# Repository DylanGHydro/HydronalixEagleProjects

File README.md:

View this project on [CADLAB.io](https://cadlab.io/project/1390). 

# HydronalixEagleProjects

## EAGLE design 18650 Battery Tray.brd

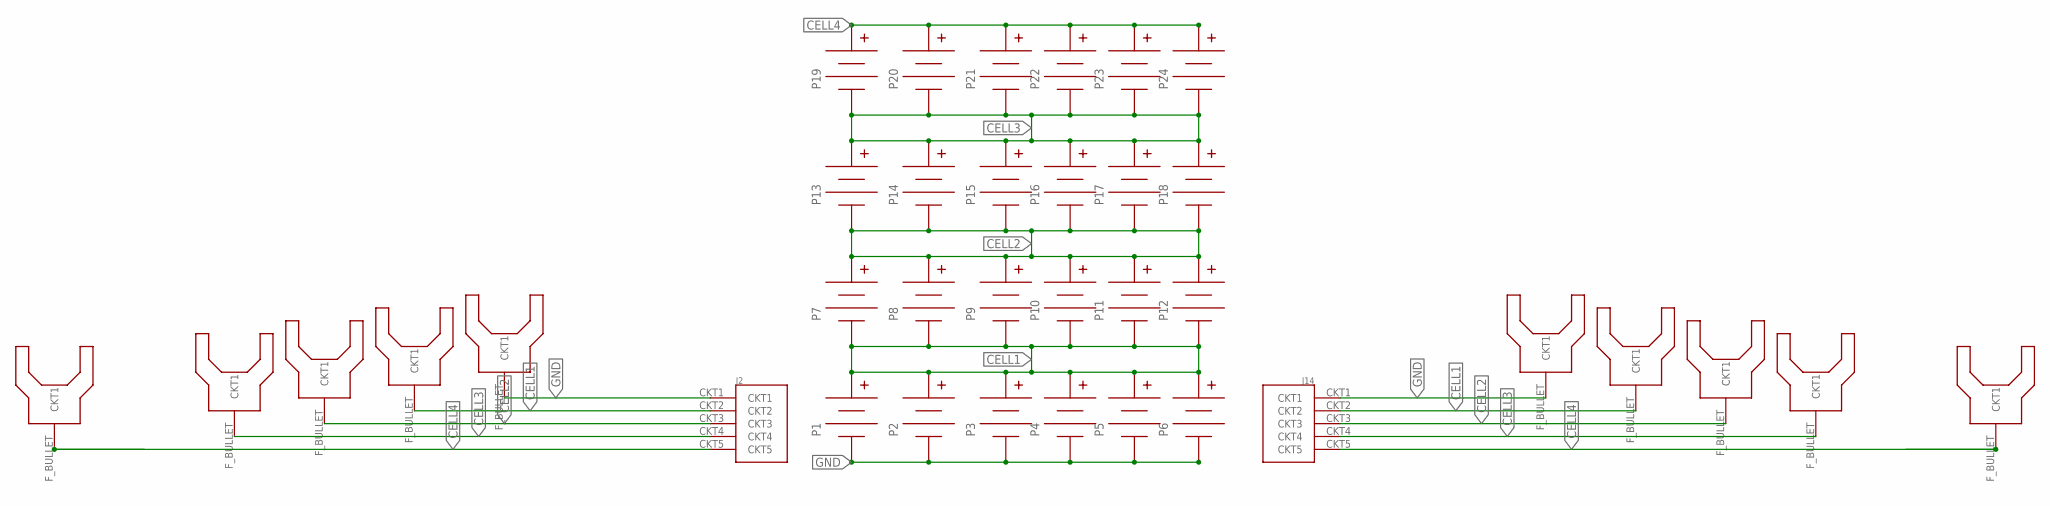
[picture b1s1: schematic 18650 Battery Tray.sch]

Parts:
J1, J3, J4, J5, J7, J9, J10, J11, J12, J15: FEMALE_BULLET; FEMALE_BULLET_CONNECTOR_6MM
J2, J14: MOLEX_NANO_FIT_5CT_VERTICAL_HEADER; MOLEX_NANO_FIT_5_VERTICAL_HEADER
P1, P2, P3, P4, P5, P6, P7, P8, P9, P10, P11, P12, P13, P14, P15, P16, P17, P18, P19, P20, P21, P22, P23, P24: 18650_BAT_TRAY_SMD_NON_POLAR

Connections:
CELL1: J2.CKT2, J3.F_BULLET, J10.F_BULLET, J14.CKT2, P1.P$2 (V+), P2.P$2 (V+), P3.P$2 (V+), P4.P$2 (V+), P5.P$2 (V+), P6.P$2 (V+), P7.P$1 (V-), P8.P$1 (V-), P9.P$1 (V-), P10.P$1 (V-), P11.P$1 (V-), P12.P$1 (V-)
CELL2: J2.CKT3, J4.F_BULLET, J11.F_BULLET, J14.CKT3, P7.P$2 (V+), P8.P$2 (V+), P9.P$2 (V+), P10.P$2 (V+), P11.P$2 (V+), P12.P$2 (V+), P13.P$1 (V-), P14.P$1 (V-), P15.P$1 (V-), P16.P$1 (V-), P17.P$1 (V-), P18.P$1 (V-)
CELL3: J2.CKT4, J5.F_BULLET, J12.F_BULLET, J14.CKT4, P13.P$2 (V+), P14.P$2 (V+), P15.P$2 (V+), P16.P$2 (V+), P17.P$2 (V+), P18.P$2 (V+), P19.P$1 (V-), P20.P$1 (V-), P21.P$1 (V-), P22.P$1 (V-), P23.P$1 (V-), P24.P$1 (V-)
CELL4: J2.CKT5, J7.F_BULLET, J14.CKT5, J15.F_BULLET, P19.P$2 (V+), P20.P$2 (V+), P21.P$2 (V+), P22.P$2 (V+), P23.P$2 (V+), P24.P$2 (V+)
GND: J1.F_BULLET, J2.CKT1, J9.F_BULLET, J14.CKT1, P1.P$1 (V-), P2.P$1 (V-), P3.P$1 (V-), P4.P$1 (V-), P5.P$1 (V-), P6.P$1 (V-)

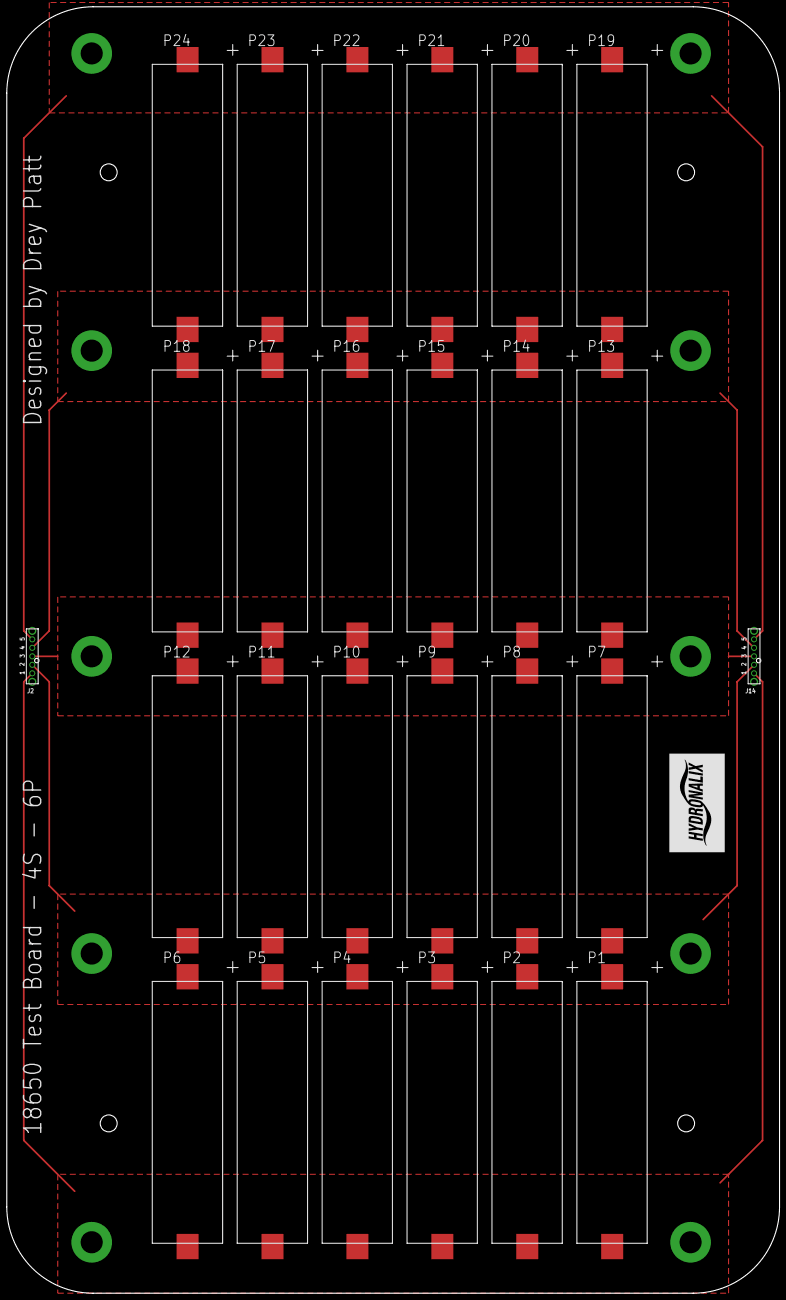
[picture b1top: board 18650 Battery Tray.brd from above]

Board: 2 copper layers, 227.5 x 378.7 mm, 36 parts (1 on the bottom side), 5 nets.

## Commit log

2018-10-25 First Commit
    1st
2018-10-25 Backlink to CADLAB.io has been added.
2018-10-30 Update 2
    Updates to board
2018-10-30 Update 18650 Battery Tray.brd
    Update 3
2018-11-01 added library
2018-11-01 added lib
